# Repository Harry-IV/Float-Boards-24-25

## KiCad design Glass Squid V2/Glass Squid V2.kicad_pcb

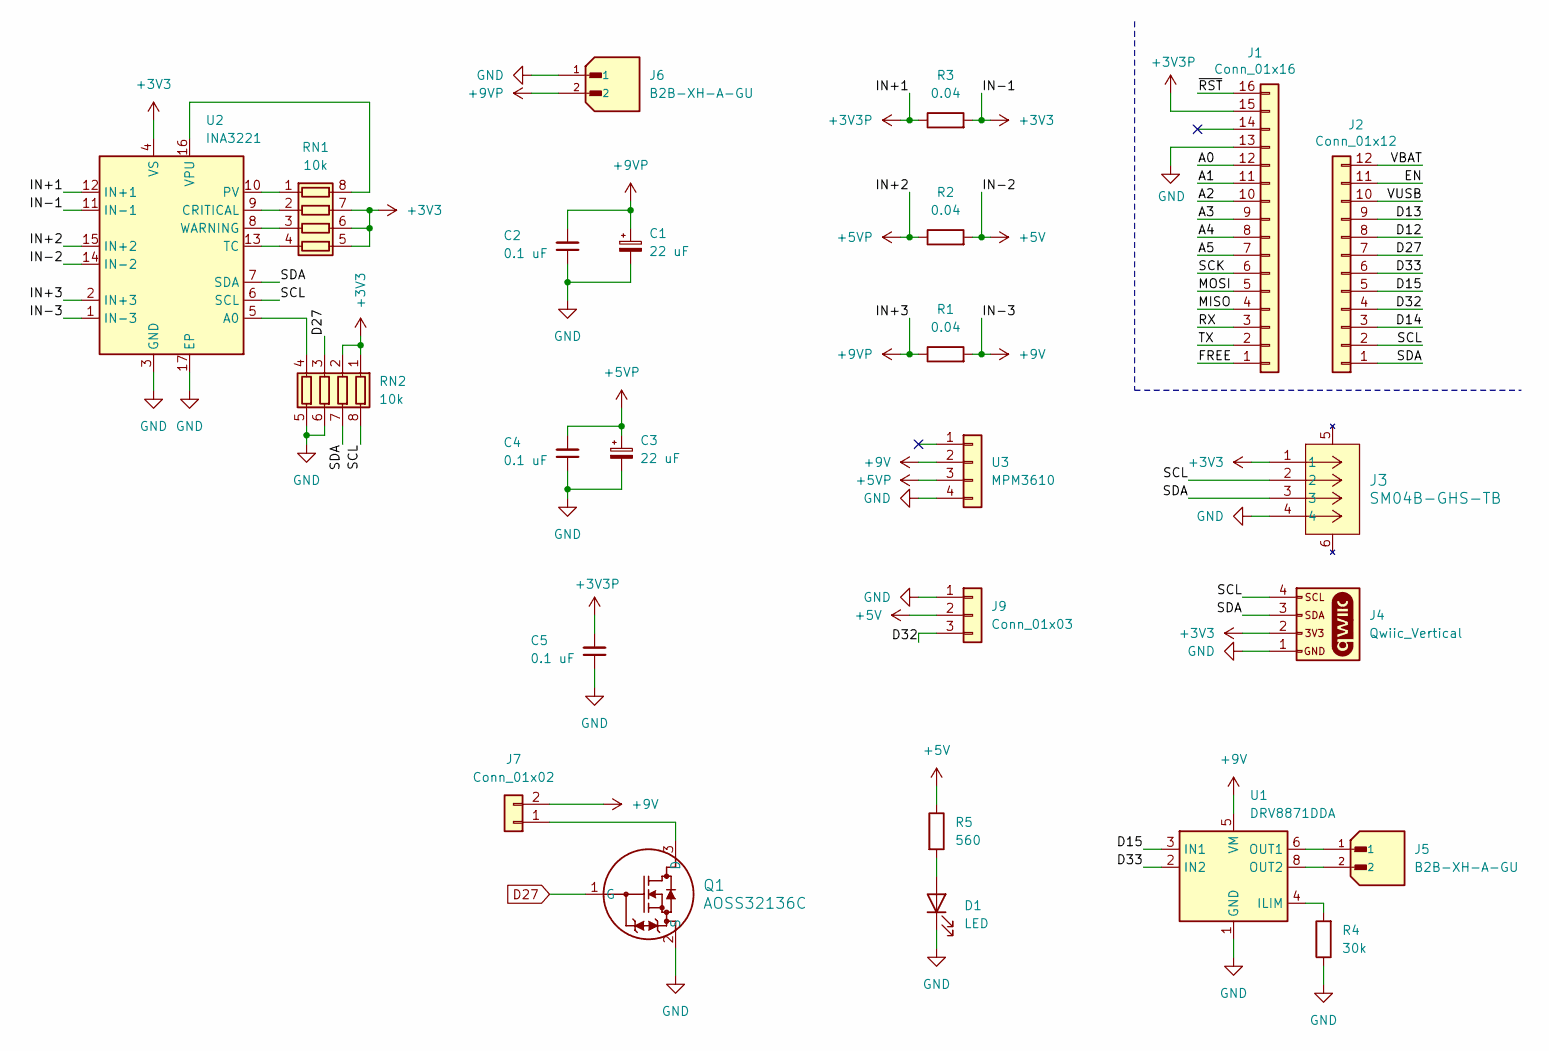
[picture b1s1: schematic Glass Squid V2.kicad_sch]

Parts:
C1, C3: 22 uF; CAP_ZC_C_PAN; Part # EEH-ZA1J220XP
C2, C4, C5: 0.1 uF; CAPC2012X140N; Part # C0805C104J5RACAUTO
D1: LED; WL-SMCW_0805; Part # 150080RS75000
J1: Conn_01x16; PinHeader_1x16_P2.54mm_Vertical; Part # N/A
J2: Conn_01x12; PinHeader_1x12_P2.54mm_Vertical; Part # N/A
J3: SM04B-GHS-TB; CONN_SM04B-GHS-TB_JST; Part # SM04B-GHS-TB
J4: Qwiic_Vertical; JST_SMD_1.0mm-4_Vertical; Part # BM04B-SRSS-TB
J5, J6: B2B-XH-A-GU; B2B-XH-A; Part # B2B-XH-A-GU
J7: Conn_01x02; PinHeader_1x02_P2.54mm_Vertical; Part # 215297-2
J9: Conn_01x03; PinHeader_1x03_P2.54mm_Vertical; Part # 61300311121
Q1: AOSS32136C; SOT23_AOS; Part # AOSS32136C
R1, R2, R3: 0.04; RES_VISHAY_WSLP0805_VIS; Part # WSLP0805R0400DEA
R4: 30k; RESC2012X60N; Part # SG73S2ATTD3002F
R5: 560; RES_CHP0805_BRN; Part # CHP0805AFX-5600ELF
RN1, RN2: 10k; EXB38V_PAN; Part # EXB-38V103JV
U1: DRV8871DDA; Texas_HTSOP-8-1EP_3.9x4.9mm_P1.27mm_EP2.95x4.9mm_Mask2.4x3.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; Part # DRV8871DDARQ1
U2: INA3221; Texas_RGV0016A_VQFN-16-1EP_4x4mm_P0.65mm_EP2.1x2.1mm; Part # INA3221AQRGVRQ1
U3: MPM3610; PinHeader_1x04_P2.54mm_Vertical; Part # 4739

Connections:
+3V3: J3.1, J4.2, R3.2, RN1.5 (R4.2), RN1.6 (R3.2), RN1.7 (R2.2), RN2.1 (R1.1), RN2.2 (R2.1), U2.4 (VS), U2.11 (IN-1)
+3V3P: C5.2, J1.15, R3.1, U2.12 (IN+1)
+5V: J9.2, R2.2, R5.1, U2.14 (IN-2)
+5VP: C3.1, C4.2, R2.1, U2.15 (IN+2), U3.3
+9V: J7.2, R1.2, U1.5 (VM), U2.1 (IN-3), U3.2
+9VP: C1.1, C2.2, J6.2, R1.1, U2.2 (IN+3)
/A0: J1.12
/A1: J1.11
/A2: J1.10
/A3: J1.9
/A4: J1.8
/A5: J1.7
/D12: J2.8
/D13: J2.9
/D14: J2.3
/D15: J2.5, U1.3 (IN1)
/D32: J2.4, J9.3
/D33: J2.6, U1.2 (IN2)
/EN: J2.11
/FREE: J1.1
/MISO: J1.4
/MOSI: J1.5
/RX: J1.3
/SCK: J1.6
/SCL: J2.2, J3.2, J4.4, RN2.8 (R1.2), U2.6 (SCL)
/SDA: J2.1, J3.3, J4.3, RN2.7 (R2.2), U2.7 (SDA)
/TX: J1.2
/VBAT: J2.12
/VUSB: J2.10
/~RST: J1.16
D27: J2.7, Q1.1 (G), RN2.3 (R3.1)
GND: C1.2, C2.1, C3.2, C4.1, C5.1, D1.1 (K), J1.13, J3.4, J4.1, J6.1, J9.1, Q1.2 (S), R4.1, RN2.5 (R4.2), RN2.6 (R3.2), U1.1 (GND), U1.7 (GND), U1.9 (GND), U2.3 (GND), U2.17 (EP), U3.4
unnamed: D1.2 (A), R5.2
unnamed: J7.1, Q1.3 (D)
unnamed: RN1.1 (R1.1), U2.10 (PV)
unnamed: RN1.8 (R1.2), U2.16 (VPU)
unnamed: RN1.2 (R2.1), U2.9 (CRITICAL)
unnamed: RN1.3 (R3.1), U2.8 (WARNING)
unnamed: RN1.4 (R4.1), U2.13 (TC)
unnamed: RN2.4 (R4.1), U2.5 (A0)
unnamed: R4.2, U1.4 (ILIM)
unnamed: J5.1, U1.6 (OUT1)
unnamed: J5.2, U1.8 (OUT2)

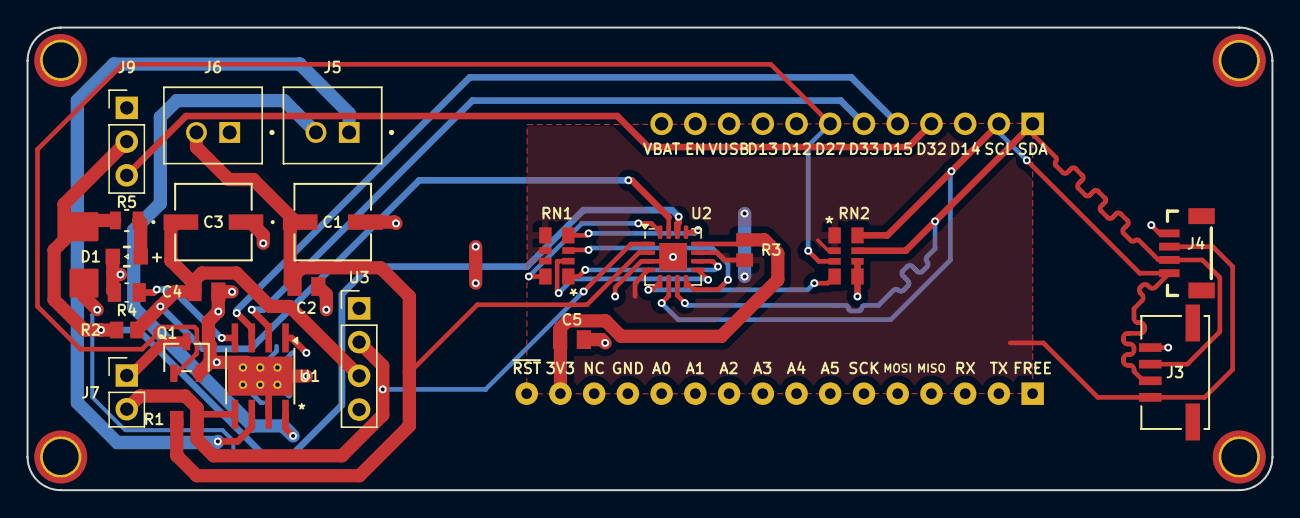
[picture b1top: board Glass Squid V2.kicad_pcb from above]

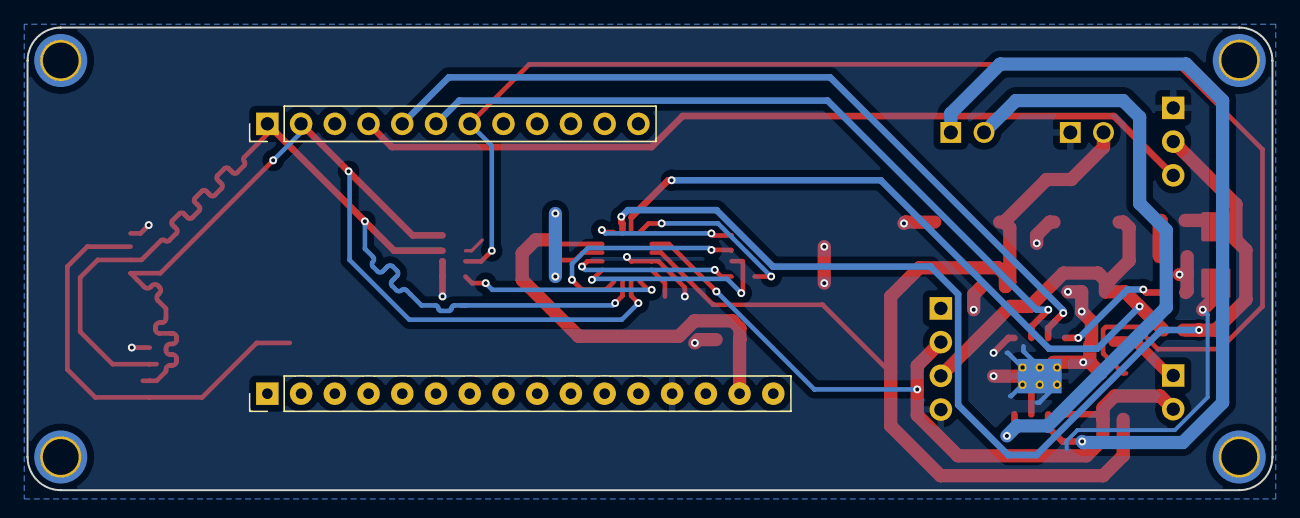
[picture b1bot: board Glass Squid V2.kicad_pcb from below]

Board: 2 copper layers, 93.8 x 34.8 mm, 25 parts (2 on the bottom side), 24 nets.

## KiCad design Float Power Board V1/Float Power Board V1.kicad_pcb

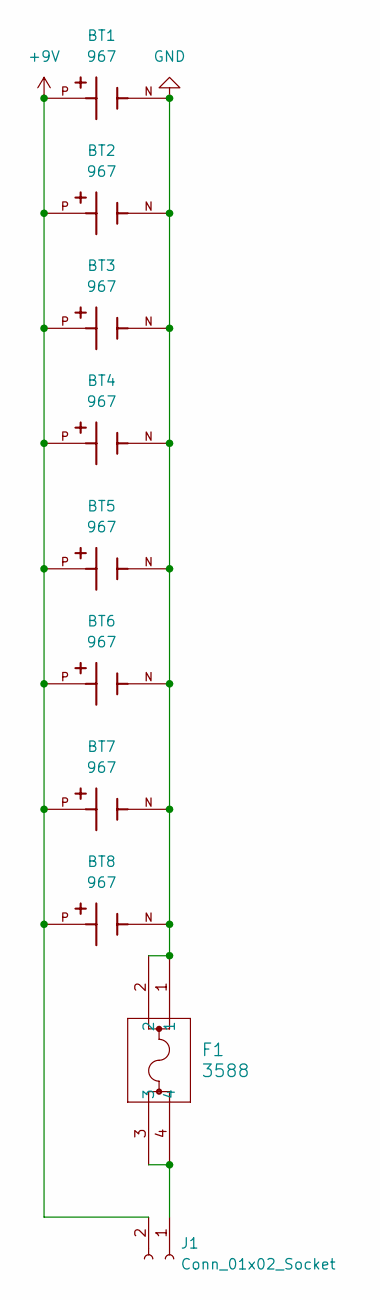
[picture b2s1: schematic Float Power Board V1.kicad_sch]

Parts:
BT1, BT2, BT3, BT4, BT5, BT7, BT8: 967; 9V Battery Holder; Part # 967
BT6: 967; 9V Battery Holder
F1: 3588; 3588_KEY; Part # 3588
J1: Conn_01x02_Socket; AMASS_XT30U-M_1x02_P5.0mm_Vertical

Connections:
+9V: BT1.P, BT2.P, BT3.P, BT4.P, BT5.P, BT6.P, BT7.P, BT8.P, J1.2
GND: BT1.N, BT2.N, BT3.N, BT4.N, BT5.N, BT6.N, BT7.N, BT8.N, F1.1, F1.2
unnamed: F1.3, F1.4, J1.1

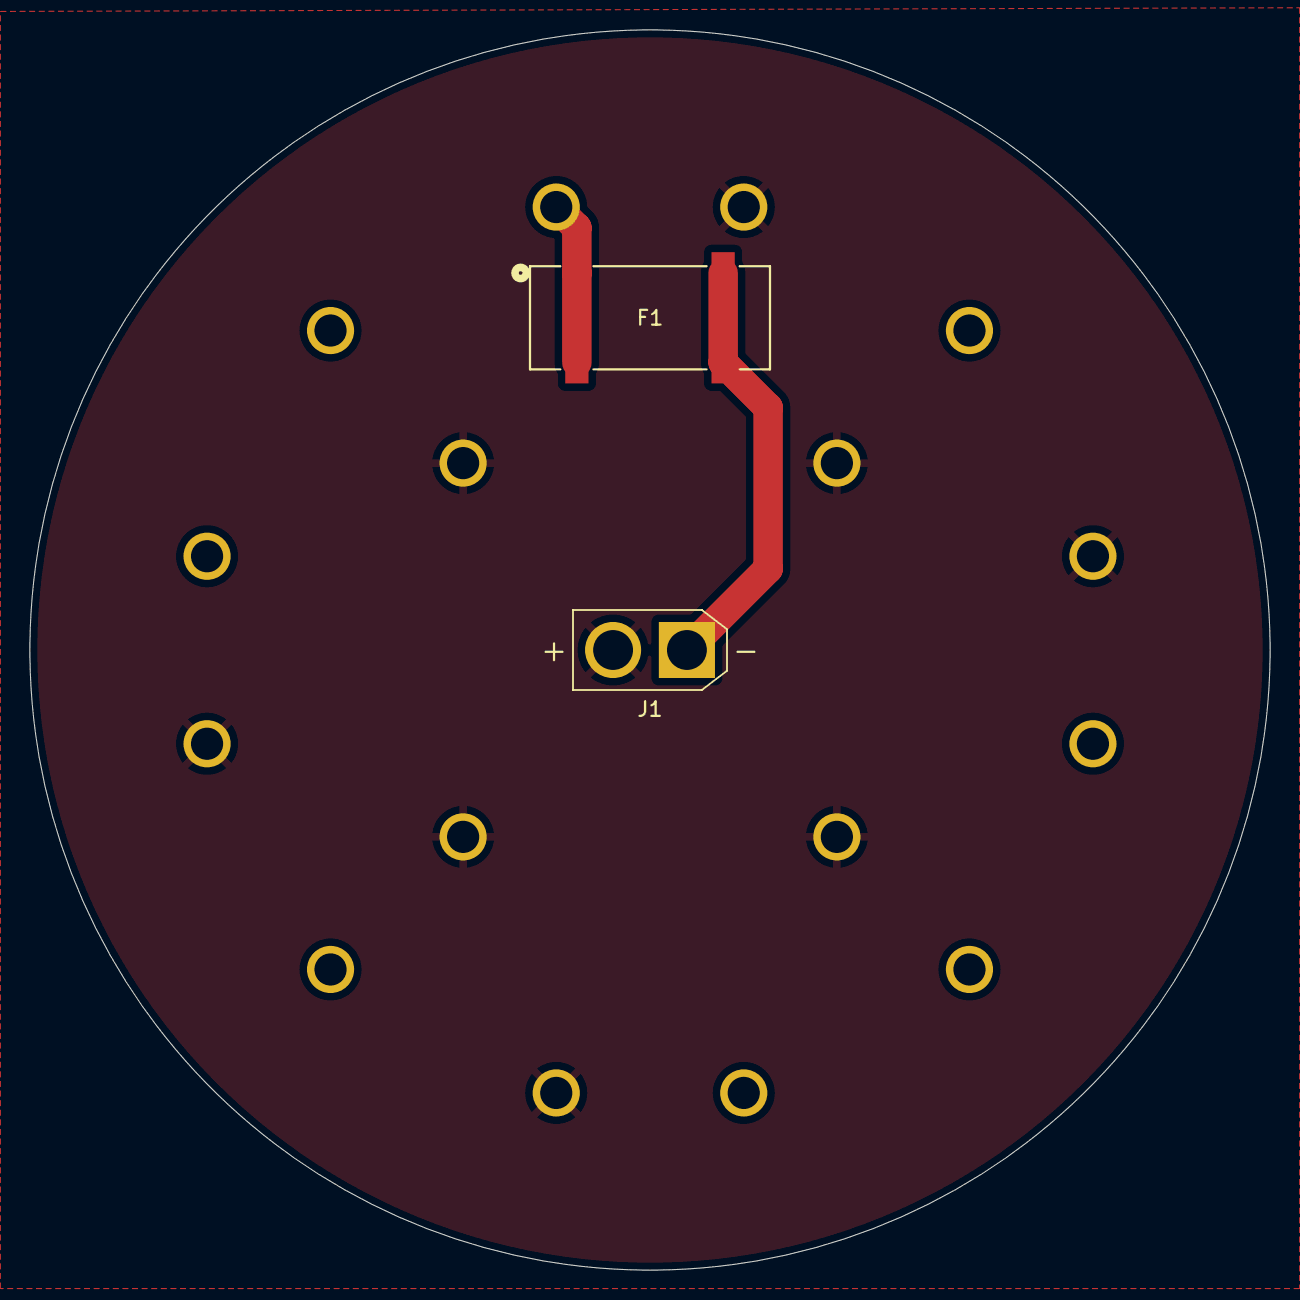
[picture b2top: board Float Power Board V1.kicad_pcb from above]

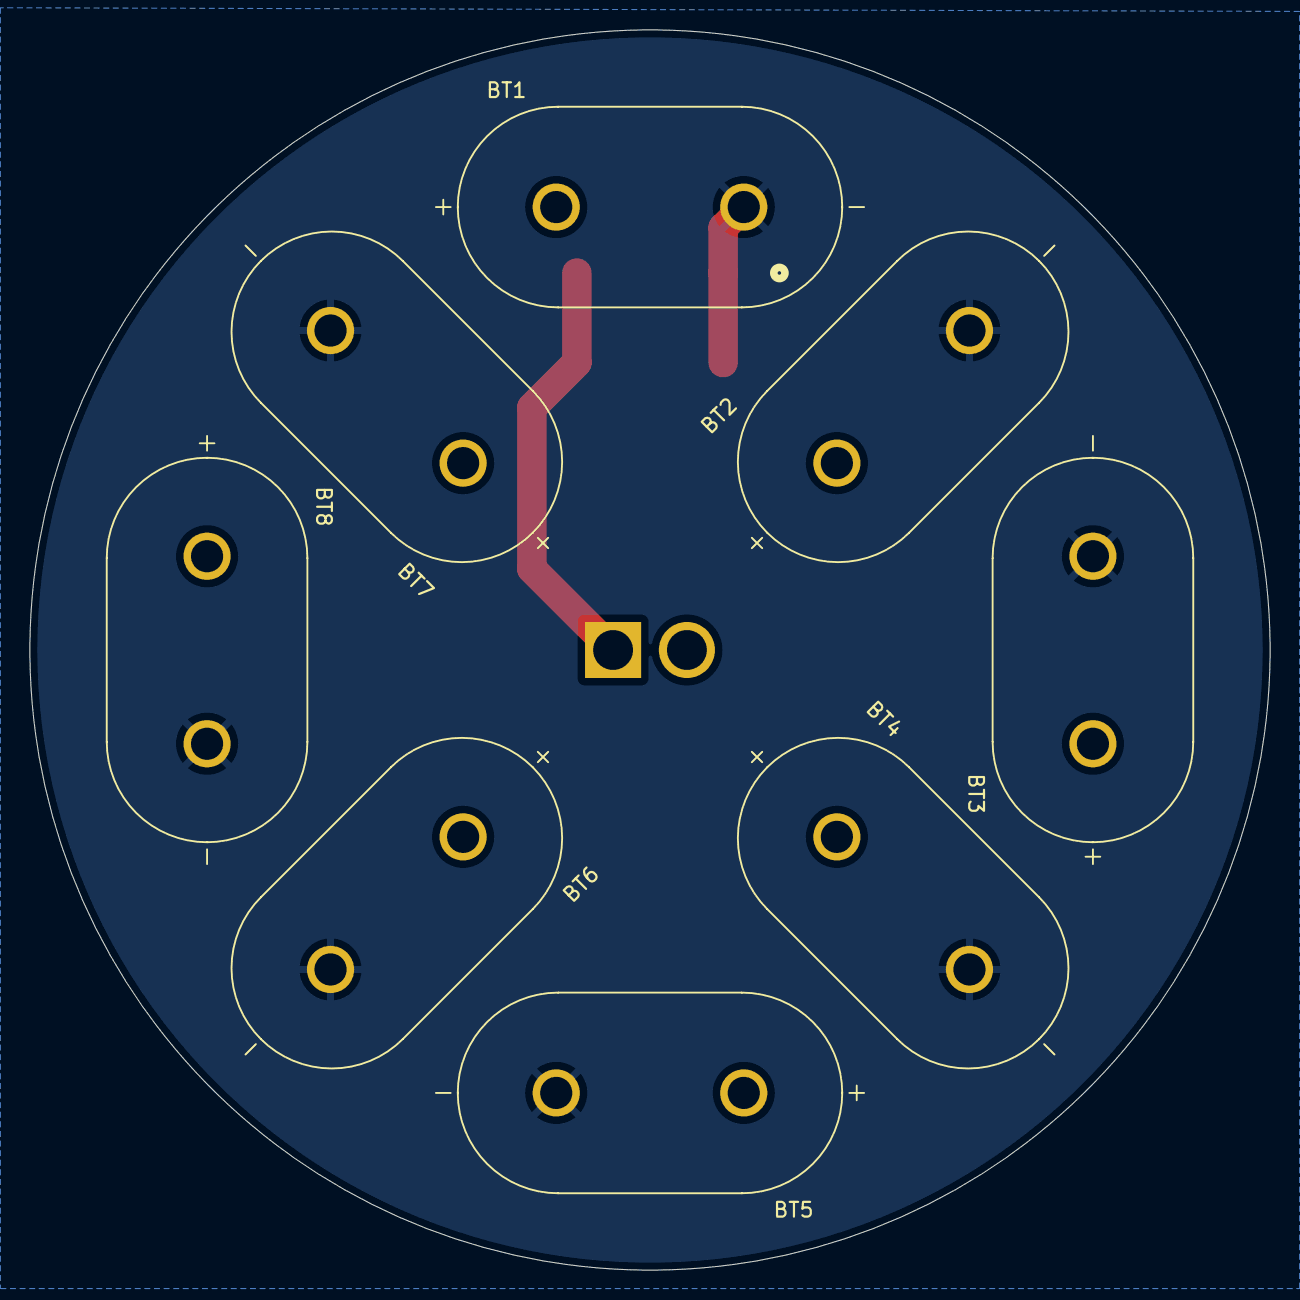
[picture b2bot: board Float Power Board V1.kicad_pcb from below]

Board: 2 copper layers, 84.0 x 84.0 mm, 10 parts (8 on the bottom side), 3 nets.

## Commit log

2025-02-15 Initial commit of boards. Not ordered yet.
2025-02-15 Fixed some warnings in Glass Squid V2
2025-02-15 Removed redundant folder.
2025-02-20 Made top board the pogo board and bulkhead the pad board.
2025-02-20 Fixed alingment pin placement and sizing for pogo and pad boards.
2025-02-20 Precautionary commit
2025-02-20 Finally fixed the issues with folder and file naming.
2025-02-20 Created interactive BOMs for Pogo and pad boards.
2025-02-23 V1 of Float Boards ... most likely :)
2025-02-23 Created .zip files and ordered the boards.
